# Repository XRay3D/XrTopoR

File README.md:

# XrTopoR

Редактор печатных плат с топологическим трассировщиком в духе TopoR: трассы под любым углом и дугами,
без сетки, топология первична — геометрия вычисляется из неё. C++26, Qt 6, CGAL, Boost.

## Сборка

```sh
cmake --preset release          # GCC 16 из /opt/gcc-16, C++26
cmake --build --preset release
ctest --preset release          # юнит-тесты + GUI-тесты (offscreen)
```

Цели: `xrtopor` (GUI), `xrtopor-cli`, библиотеки `xrgeom`, `xrcore`, `xrio`, `xrdrc`, `xrrouter`, `xrgui`.

## Форматы

| Формат | Чтение | Запись |
|---|---|---|
| KiCad `.kicad_pcb` (6–11) + `.kicad_pro` (классы цепей) | да | да (исходный файл патчится: размещение и разводка, остальное сохраняется) |
| Specctra `.dsn` / `.ses` | да | да |
| P-CAD 2002 ASCII `.pcb` | да | — |
| Gerber RS-274X (X2) + Excellon | — | да |
| SVG (просмотр) | — | да |

## CLI

```sh
xrtopor-cli info    board.kicad_pcb
xrtopor-cli route   board.dsn -o routed.ses [--passes 6] [--via-cost 3] [--no-vias] [--nets a,b] [--svg out.svg]
xrtopor-cli drc     board.kicad_pcb [--max N]
xrtopor-cli convert board.pcb out.kicad_pcb
xrtopor-cli import-ses board.dsn routes.ses -o out.dsn
xrtopor-cli gerber  board.kicad_pcb outdir/
xrtopor-cli svg     board.kicad_pcb out.svg
```

## GUI: горячие клавиши (как в TopoR)

| Клавиша | Действие |
|---|---|
| `R` | режим прокладки проводников: клик по площадке — старт, клики — точки, клик по площадке той же цепи / Enter / двойной клик — финиш |
| `V` | во время прокладки — переходное отверстие и смена слоя; иначе режим постановки переходов |
| `L` | следующий медный слой (при прокладке — через переход) |
| `1`…`9`, `0` | активный медный слой (0 — нижний) |
| `O` / `A` | ограничение 45° / режим дуг (дуга касательна к предыдущему сегменту) |
| `W` | ширина проводника |
| `Backspace` | убрать последний сегмент при прокладке |
| `Esc` | отмена прокладки / режим выделения |
| `Space`, `Shift+Space` | повернуть компонент на −90° / +90° |
| `Del` | удалить выделенное |
| `N` | показать/скрыть связи |
| `Shift+S` | только активный медный слой |
| `Ctrl+B` | показать плату целиком |
| `F9` | DRC |
| `F10` | автотрассировка (в фоне, с отменой) |
| `Ctrl+Z` / `Ctrl+Y` | отмена / повтор |
| колесо / средняя или правая кнопка | масштаб / панорамирование |

Резиновый сегмент при прокладке краснеет, если нарушает зазор (онлайн-DRC).

## Трассировщик (`src/router/topo`)

1. `TopoMesh` — ограниченная триангуляция Делоне (CGAL) по центрам и углам площадок, переходным отверстиям,
   кандидатам переходов и контуру платы.
2. `TopoRouter` — поиск A* по состояниям (треугольник, ребро входа, позиция в порядке пересечений) с
   проверкой планарности хорд, негоциация перегрузок рёбер (PathFinder), rip-up & reroute, переходы в
   вершинах-кандидатах, геометрическая обратная связь (реализация → проверка → штраф → перетрассировка).
3. `Realizer` — для каждой топологии: воронка в триангуляции препятствий, вложенность трасс вокруг
   общих препятствий, утолщение в касательные отрезки + дуги.

Отладочные переменные окружения: `XR_SKETCH=1` (выдать топологические эскизы вместо геометрии),
`XR_DEBUG`, `XR_DEBUG2`, `XR_DEBUG3`, `XR_DEBUG4`, `XR_NONEST`.

## Тестовые платы

`tests/data/`: платы KiCad (`astable`, `tt`, `adg508f_tester_v11`), DSN/SES (`adg508f_single`),
P-CAD ASCII (`el4134_pcad_ascii.pcb`), примеры TopoR (`topor/Example_0x`: мастера + разводки `.fst`).

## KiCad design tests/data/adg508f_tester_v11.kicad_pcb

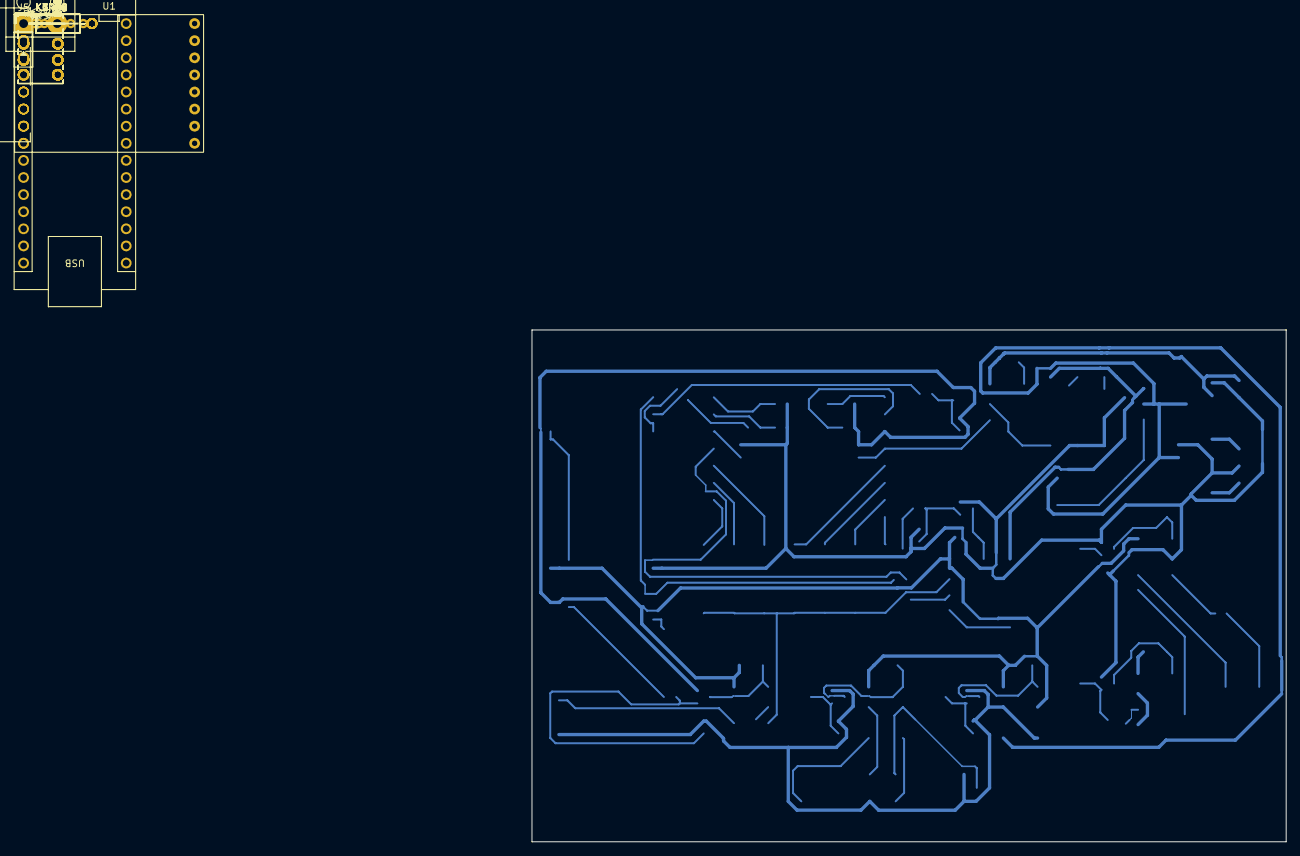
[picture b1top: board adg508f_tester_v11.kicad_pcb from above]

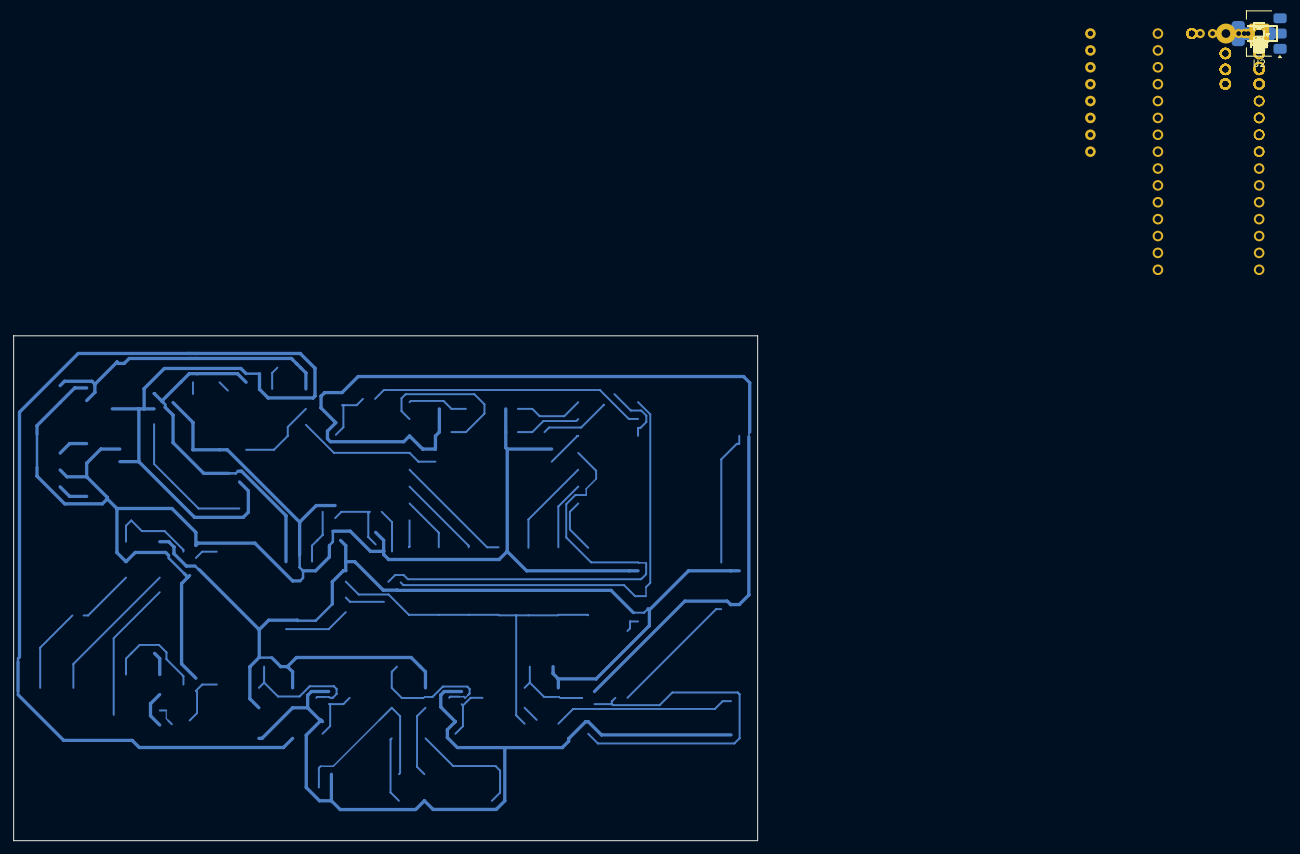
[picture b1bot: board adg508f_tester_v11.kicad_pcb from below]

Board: 2 copper layers, 112.0 x 76.0 mm, 80 parts (45 on the bottom side), 63 nets.

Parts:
A1: NUCLEO-G431KB; Arduino_Nano
C1, C2, C7: 0.1u; C_0805_2012Metric
C3: 4.7u; C_0805_2012Metric
C4, C5: 10u 50V; C_1206_3216Metric
C6: 33p C0G; C_0805_2012Metric
C8: 1u; C_0805_2012Metric
D1, D2, D3, D4, D5, D6, D7: LL4148; D_MiniMELF
J5: Осциллограф (PLS-3); PinHeader_1x03_P2.54mm_Vertical
K1, K2, K3, K4, K5, K6, K7: G6K-2P-Y 5V; Relay_DPDT_Omron_G6K-2P-Y
PS1: E0515S-1WR3; Converter_DCDC_Mornsun_E_S-1WR3_Dual_THT
Q1, Q2, Q3, Q4, Q5, Q6, Q7: 2N7002; SOT-23
R1, R2, R3, R4: 1k; R_0805_2012Metric
R5, R6, R7, R8, R13, R25, R32, R34, R36, R38, R40: 100k; R_0805_2012Metric
R9, R10, R11: 100; R_Axial_DIN0207_L6.3mm_D2.5mm_P10.16mm_Horizontal
R12, R24, R31, R33, R35, R37, R39: 100; R_0805_2012Metric
R17: 499; R_Axial_DIN0207_L6.3mm_D2.5mm_P10.16mm_Horizontal
R18, R29: 1k; R_Axial_DIN0207_L6.3mm_D2.5mm_P10.16mm_Horizontal
R19: 1.5k; R_Axial_DIN0207_L6.3mm_D2.5mm_P10.16mm_Horizontal
R20: 2k; R_Axial_DIN0207_L6.3mm_D2.5mm_P10.16mm_Horizontal
R21: 2.49k; R_Axial_DIN0207_L6.3mm_D2.5mm_P10.16mm_Horizontal
R22: 3.01k; R_Axial_DIN0207_L6.3mm_D2.5mm_P10.16mm_Horizontal
R23: 3.48k; R_Axial_DIN0207_L6.3mm_D2.5mm_P10.16mm_Horizontal
R26: 100k; R_Axial_DIN0207_L6.3mm_D2.5mm_P10.16mm_Horizontal
R27: 15k; R_Axial_DIN0207_L6.3mm_D2.5mm_P10.16mm_Horizontal
R28: 10M; R_Axial_DIN0207_L6.3mm_D2.5mm_P10.16mm_Horizontal
R30: 10k; R_Axial_DIN0207_L6.3mm_D2.5mm_P10.16mm_Horizontal
R41: 240; R_Axial_DIN0207_L6.3mm_D2.5mm_P10.16mm_Horizontal
R42: 1.68k; R_Axial_DIN0207_L6.3mm_D2.5mm_P10.16mm_Horizontal
U1: ADG508FB (DUT); DIP-16_W25.4mm_Socket
U2: LM317; SOT-223-3_TabPin2
W1: Wire 8.9 mm; Jumper_Wire_L8.87mm
W2: Wire 3.1 mm; Jumper_Wire_L3.08mm
W3: Wire 2.2 mm; Jumper_Wire_L2.25mm
W4: Wire 4.8 mm; Jumper_Wire_L4.83mm
W5: Wire 7.0 mm; Jumper_Wire_L7.01mm
W6: Wire 1.7 mm; Jumper_Wire_L1.67mm
XT2: 34401A HI/LO; Altech_AK100_1x02_P5.00mm

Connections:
+5V: A1.27 (+5V), C3.1, D1.1 (K), D2.1 (K), D3.1 (K), D4.1 (K), D5.1 (K), D6.1 (K), D7.1 (K), K1.1, K2.1, K3.1, K4.1, K5.1, K6.1, K7.1, K7.7, PS1.1 (Vin)
+10V: C8.1, K7.4, R41.1, U2.2 (VO)
+15V: C4.1, C7.1, K4.2, K4.4, PS1.7 (+Vo), R9.1, R26.1, R27.1, U2.3 (VI)
-15V: C5.2, K1.7, PS1.5 (-Vo)
/BUS_S: K2.2, K5.6, R17.2, R18.2, R19.2, R20.2, R21.2, R22.2, R23.2
/DA: K5.2, K6.3
/DB: K5.4, K6.6
/DIS_N: K1.5, R11.1
/DIS_P: K1.4, R10.1
/DL1: K6.2, R27.2
/DL2: K6.4, R28.1
/DL3: C6.1, K6.7, R29.1
/DL4: K6.5, R30.1
/DMM_HI: K3.3, XT2.1
/DMM_LO: K3.6, W6.1, W6.2, XT2.2
/D_OUT: J5.1, K3.2, K5.3, U1.8 (D)
/MCU_A0: A1.5 (D2), R1.1
/MCU_A1: A1.6 (D3), R2.1
/MCU_A2: A1.9 (D6), R3.1
/MCU_EN: A1.12 (D9), R4.1, W3.1, W3.2
/MUX_A0: J5.2, R1.2, R5.1, U1.1 (A0)
/MUX_A1: R2.2, R6.1, U1.16 (A1)
/MUX_A2: R3.2, R7.1, U1.15 (A2)
/MUX_EN: R4.2, R8.1, U1.2 (EN)
/M_HI: K3.4, K4.3, W1.1, W1.2
/M_LO: K3.5, K4.6
/RLY_K1: A1.13 (D10), R12.1
/RLY_K2: A1.14 (D11), R24.1, W4.1, W4.2
/RLY_K3: A1.2 (D0/RX), R31.1
/RLY_K4: A1.1 (D1/TX), R33.1
/RLY_K5: A1.19 (A0), R35.1, W5.1, W5.2
/RLY_K6: A1.20 (A1), R37.1
/RLY_K7: A1.22 (A3), R39.1
/S1: K2.3, U1.4 (S1), W2.1, W2.2
/S2: R17.1, U1.5 (S2)
/S3: R18.1, U1.6 (S3)
/S4: R19.1, U1.7 (S4)
/S5: R20.1, U1.12 (S5)
/S6: R21.1, U1.11 (S6)
/S7: R22.1, U1.10 (S7)
/S8: R23.1, U1.9 (S8)
/SA: K5.7, K7.3
/SB: K5.5, K7.6
/VDD_DUT: C1.1, K1.3, U1.13 (VDD)
/VDD_SH: K1.2, K4.7, R9.2
/VF_R: K2.4, K4.5, R26.2
/VSS_DUT: C2.1, K1.6, U1.3 (VSS)
GND: A1.4 (GND), A1.29 (GND), C1.2, C2.2, C3.2, C4.2, C5.1, C6.2, C7.2, C8.2, J5.3, K3.7, K7.2, K7.5, PS1.2 (GND), PS1.6 (0V), Q1.2 (S), Q2.2 (S), Q3.2 (S), Q4.2 (S), Q5.2 (S), Q6.2 (S), Q7.2 (S), R5.2, R6.2, R7.2, R8.2, R10.2, R11.2, R13.2, R25.2, R28.2, R29.2, R30.2, R32.2, R34.2, R36.2, R38.2, R40.2, R42.2, U1.14 (GND)
unnamed: D1.2 (A), K1.8, Q1.3 (D)
unnamed: D2.2 (A), K2.8, Q2.3 (D)
unnamed: D3.2 (A), K3.8, Q3.3 (D)
unnamed: D4.2 (A), K4.8, Q4.3 (D)
unnamed: D5.2 (A), K5.8, Q5.3 (D)
unnamed: D6.2 (A), K6.8, Q6.3 (D)
unnamed: D7.2 (A), K7.8, Q7.3 (D)
unnamed: Q1.1 (G), R12.2, R13.1
unnamed: Q2.1 (G), R24.2, R25.1
unnamed: Q3.1 (G), R31.2, R32.1
unnamed: Q4.1 (G), R33.2, R34.1
unnamed: Q5.1 (G), R35.2, R36.1
unnamed: Q6.1 (G), R37.2, R38.1
unnamed: Q7.1 (G), R39.2, R40.1
unnamed: R41.2, R42.1, U2.1 (ADJ)

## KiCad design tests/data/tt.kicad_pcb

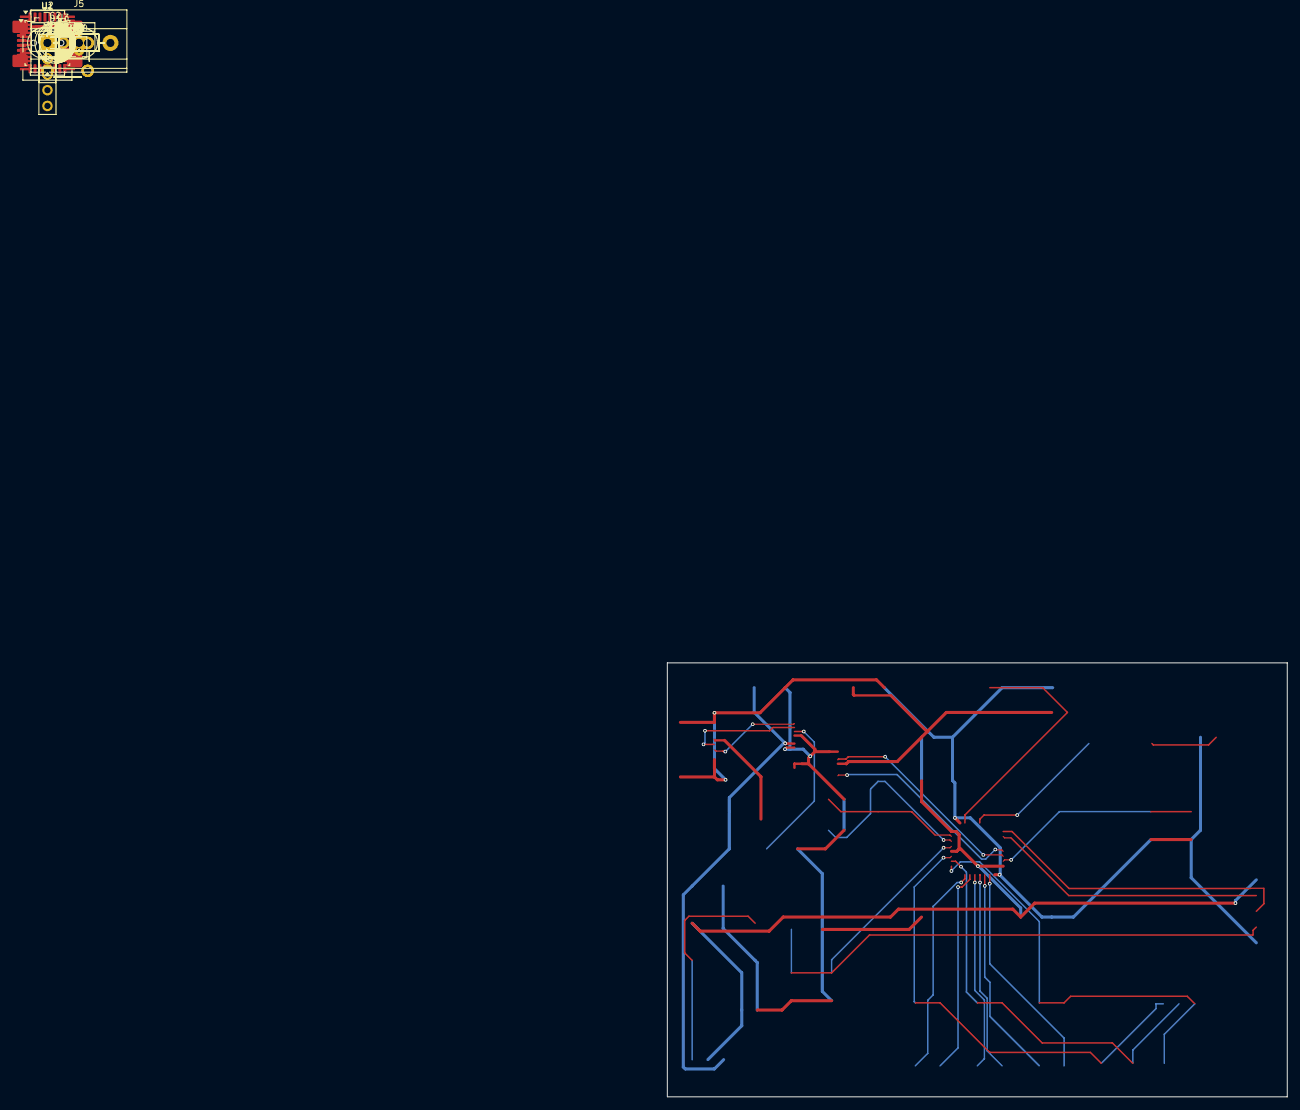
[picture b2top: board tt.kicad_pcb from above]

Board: 2 copper layers, 100.0 x 70.0 mm, 35 parts (0 on the bottom side), 28 nets.

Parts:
C1, C8: 1u; C_Disc_D5.0mm_W2.5mm_P5.00mm
C2: 100u; CP_Radial_D6.3mm_P2.50mm
C3, C4, C5, C6, C7, C12: 100n; C_Disc_D5.0mm_W2.5mm_P5.00mm
C9: 10n; C_Disc_D5.0mm_W2.5mm_P5.00mm
C10, C11: 22p; C_Disc_D3.0mm_W1.6mm_P2.50mm
D1: L-53GD; LED_D5.0mm
F1: MF-R050; Fuse_Bourns_MF-RHT050
J1: DS1104-03-BN0BT; USB_Mini-B_Wuerth_65100516121_Horizontal
J2: SWD; PinHeader_1x05_P2.54mm_Vertical
J3: BOOT0; PinHeader_1x02_P2.54mm_Vertical
J4: PBS-3 (щупы 1-2-3); PinSocket_1x03_P2.54mm_Vertical
J5: Клеммник (щупы 1-2-3); TerminalBlock_Phoenix_MKDS-1,5-3-5.08_1x03_P5.08mm_Horizont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
R1: 240; R_Axial_DIN0207_L6.3mm_D2.5mm_P10.16mm_Horizontal
R2: 383; R_Axial_DIN0207_L6.3mm_D2.5mm_P10.16mm_Horizontal
R3, R4, R5: 470 1%; R_Axial_DIN0207_L6.3mm_D2.5mm_P10.16mm_Horizontal
R6, R7, R8: 511k 1%; R_Axial_DIN0207_L6.3mm_D2.5mm_P10.16mm_Horizontal
R9: 10k; R_Axial_DIN0207_L6.3mm_D2.5mm_P10.16mm_Horizontal
R10: 470; R_Axial_DIN0207_L6.3mm_D2.5mm_P10.16mm_Horizontal
SW1: Тест; SW_PUSH_6mm
SW2: Сброс; SW_PUSH_6mm
U1: STM32F303K8T6; LQFP-32_7x7mm_P0.8mm
U2: FT232RL; SSOP-28_5.3x10.2mm_P0.65mm
U3: LM317; TO-220-3_Vertical
Y1: 16 МГц; Crystal_HC49-4H_Vertical

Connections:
+3V3: C2.1, C5.1, C6.1, C7.1, C8.1, C9.1, J2.1, J3.1, R1.1, U1.1 (VDD), U1.5 (VDDA), U1.17 (VDD), U2.4 (VCCIO), U3.2 (VO)
+5V: C1.1, C3.1, F1.1, U2.20 (VCC), U3.3 (VI)
/BOOT0: J3.2, R9.1, U1.31 (BOOT0)
/BTN: SW1.1, U1.18 (PA8)
/LED: R10.1, U1.28 (PB5)
/LM_ADJ: R1.2, R2.1, U3.1 (ADJ)
/NRST: C12.1, J2.4, SW2.1, U1.4 (NRST)
/OSC_IN: C10.1, U1.2 (PF0), Y1.1
/OSC_OUT: C11.1, U1.3 (PF1), Y1.2
/RH1: R6.1, U1.11 (PA5)
/RH2: R7.1, U1.13 (PA7)
/RH3: R8.1, U1.15 (PB1)
/RL1: R3.1, U1.10 (PA4)
/RL2: R4.1, U1.12 (PA6)
/RL3: R5.1, U1.14 (PB0)
/SWCLK: J2.3, U1.24 (PA14)
/SWDIO: J2.2, U1.23 (PA13)
/TP1: J4.1, J5.1, R3.2, R6.2, U1.6 (PA0)
/TP2: J4.2, J5.2, R4.2, R7.2, U1.7 (PA1)
/TP3: J4.3, J5.3, R5.2, R8.2, U1.8 (PA2)
/UART_RX: U1.20 (PA10), U2.1 (TXD)
/UART_TX: U1.19 (PA9), U2.5 (RXD)
/USB_DM: J1.2 (D-), U2.16 (USBD-)
/USB_DP: J1.3 (D+), U2.15 (USBD+)
/V3OUT: C4.1, U2.17 (3V3OUT)
/VBUS: F1.2, J1.1 (VBUS)
GND: C1.2, C2.2, C3.2, C4.2, C5.2, C6.2, C7.2, C8.2, C9.2, C10.2, C11.2, C12.2, D1.1 (K), J1.5 (GND), J1.SH (Shield), J2.5, R2.2, R9.2, SW1.2, SW2.2, U1.16 (VSS), U1.32 (VSS), U2.7 (GND), U2.18 (GND), U2.21 (GND), U2.25 (AGND), U2.26 (TEST)
unnamed: D1.2 (A), R10.2

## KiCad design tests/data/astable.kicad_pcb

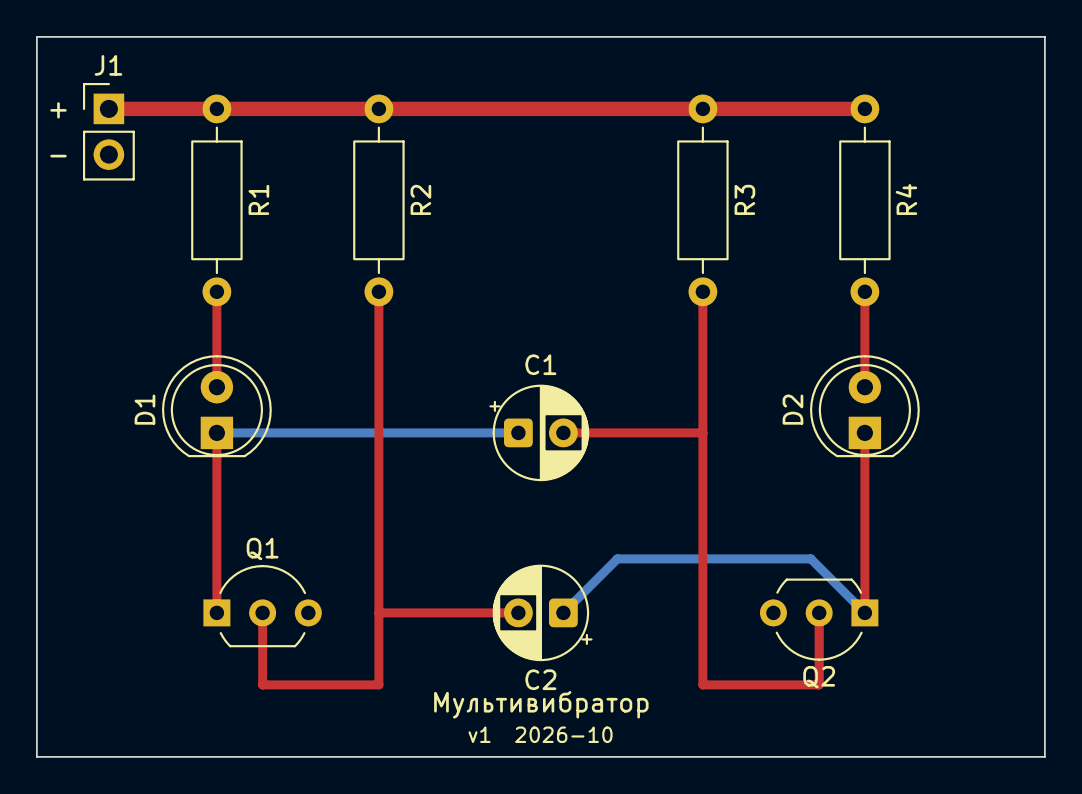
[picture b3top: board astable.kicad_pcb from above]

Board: 2 copper layers, 56.0 x 40.0 mm, 11 parts (0 on the bottom side), 8 nets.

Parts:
C1, C2: 10u; CP_Radial_D5.0mm_P2.50mm
D1, D2: RED; LED_D5.0mm
J1: +5V..9V; PinHeader_1x02_P2.54mm_Vertical
Q1, Q2: BC547; TO-92_Inline_Wide
R1, R4: 470; R_Axial_DIN0207_L6.3mm_D2.5mm_P10.16mm_Horizontal
R2, R3: 47k; R_Axial_DIN0207_L6.3mm_D2.5mm_P10.16mm_Horizontal

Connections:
GND: J1.2, Q1.3, Q2.3
unnamed: D1.2, R1.2
unnamed: C1.1, D1.1, Q1.1
unnamed: D2.2, R4.2
unnamed: C2.1, D2.1, Q2.1
unnamed: C2.2, Q1.2, R2.2
unnamed: C1.2, Q2.2, R3.2
VCC: J1.1, R1.1, R2.1, R3.1, R4.1
